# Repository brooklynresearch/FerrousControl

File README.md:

# FerrousControl
Ferrofluid controlled through an electromagnetic array

## python
This folder contains all the algorithms and code to send to the electromagnetic array.

## embedded
This folder contains all the design files and embedded code for the electromagentic controller boards.
These basically received USB Serial messages from the main computer, parse that information to the proper board, and translate those messages to the electromagnets.

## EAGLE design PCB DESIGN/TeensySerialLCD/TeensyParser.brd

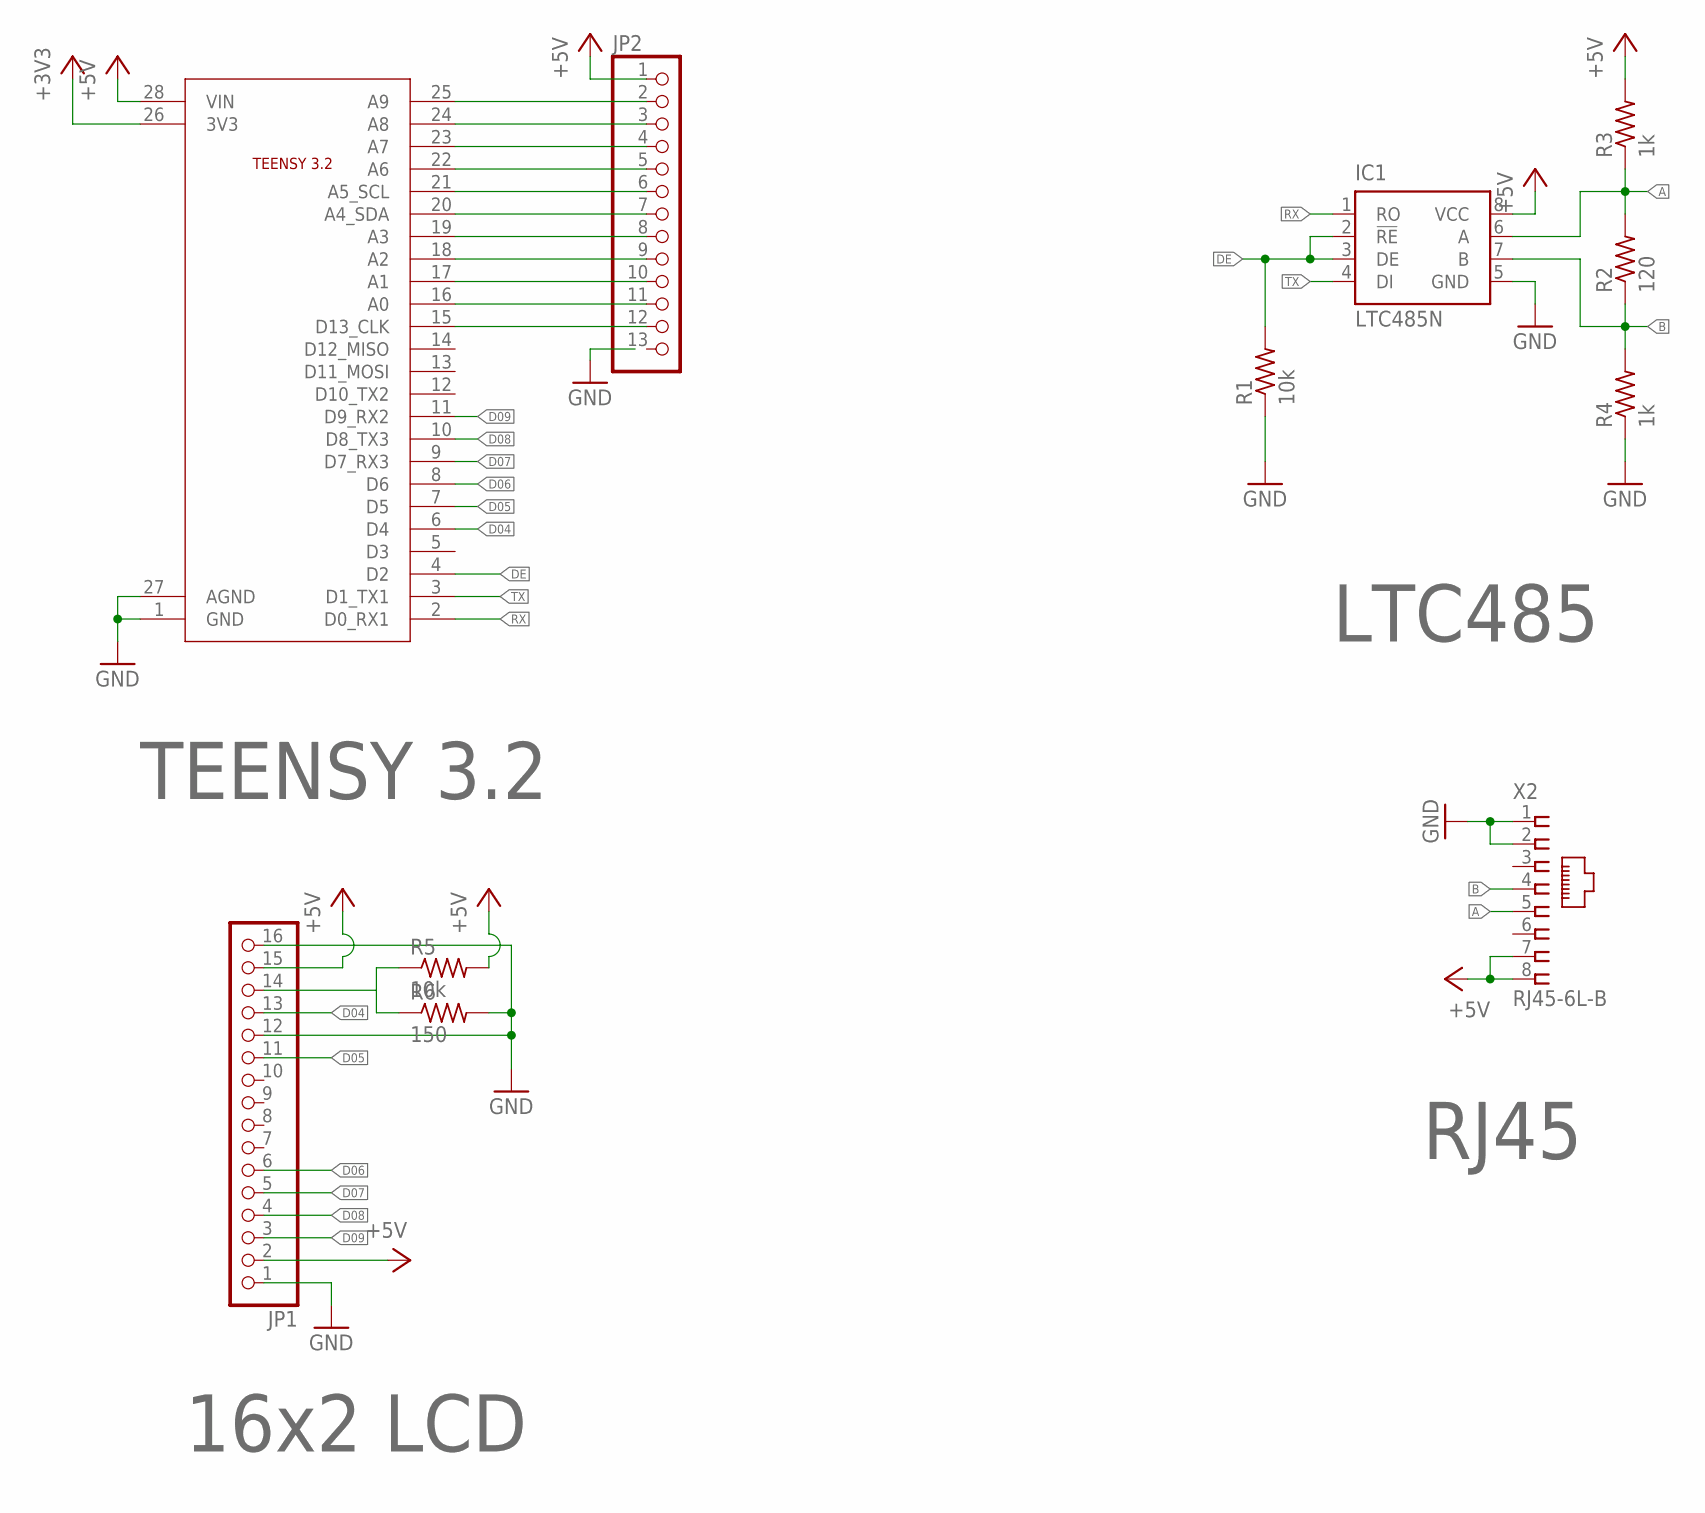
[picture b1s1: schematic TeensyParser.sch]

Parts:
IC1: LTC485N; DIL08
JP1: PINHD-1X16; 1X16
JP2: PINHD-1X13; 1X13
R1, R5: 10k; 0204/7
R2: 120; 0204/7
R3, R4: 1k; 0204/7
R6: 150; 0204/7
U$1: TEENSY3.2; TEENSY
X2: RJ45-6L-B; RJ45-NO-SHIELD

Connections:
+3V3: U$1.26 (3V3)
+5V: IC1.8 (VCC), JP1.2, JP1.15, JP2.1, R3.2, R5.2, U$1.28 (VIN), X2.7, X2.8
A: IC1.6 (A), R2.2, R3.1, X2.5
B: IC1.7 (B), R2.1, R4.2, X2.4
D04: JP1.13, U$1.6 (D4)
D05: JP1.11, U$1.7 (D5)
D06: JP1.6, U$1.8 (D6)
D07: JP1.5, U$1.9 (D7_RX3)
D08: JP1.4, U$1.10 (D8_TX3)
D09: JP1.3, U$1.11 (D9_RX2)
DE: IC1.2 (!RE), IC1.3 (DE), R1.2, U$1.4 (D2)
GND: IC1.5 (GND), JP1.1, JP1.12, JP1.16, R1.1, R4.1, R6.2, U$1.1 (GND), U$1.27 (AGND), X2.1, X2.2
unnamed: JP2.2, U$1.25 (A9)
unnamed: JP2.3, U$1.24 (A8)
unnamed: JP2.4, U$1.23 (A7)
unnamed: JP2.5, U$1.22 (A6)
unnamed: JP2.6, U$1.21 (A5_SCL)
unnamed: JP2.7, U$1.20 (A4_SDA)
unnamed: JP2.8, U$1.19 (A3)
unnamed: JP2.9, U$1.18 (A2)
unnamed: JP2.10, U$1.17 (A1)
unnamed: JP2.11, U$1.16 (A0)
unnamed: JP2.12, U$1.15 (D13_CLK)
unnamed: JP1.14, R5.1, R6.1
RX: IC1.1 (RO), U$1.2 (D0_RX1)
TX: IC1.4 (DI), U$1.3 (D1_TX1)

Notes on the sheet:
TEENSY 3.2
16x2 LCD
LTC485
RJ45

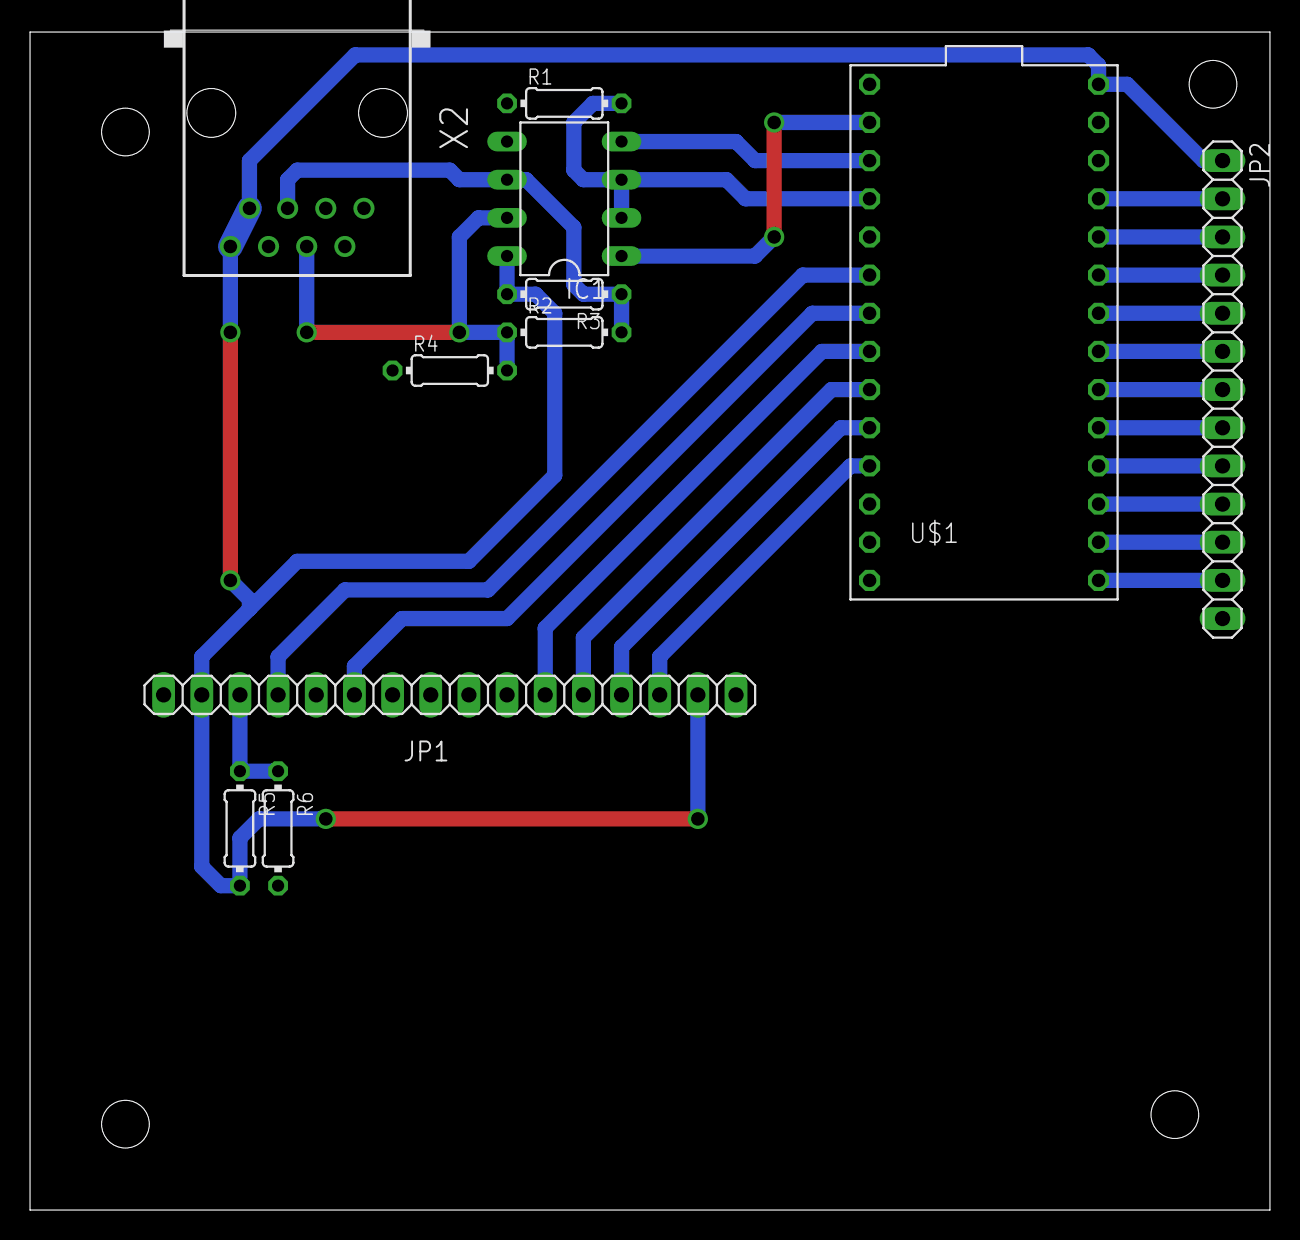
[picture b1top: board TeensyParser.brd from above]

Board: 2 copper layers, 82.5 x 78.4 mm, 11 parts (0 on the bottom side), 25 nets.

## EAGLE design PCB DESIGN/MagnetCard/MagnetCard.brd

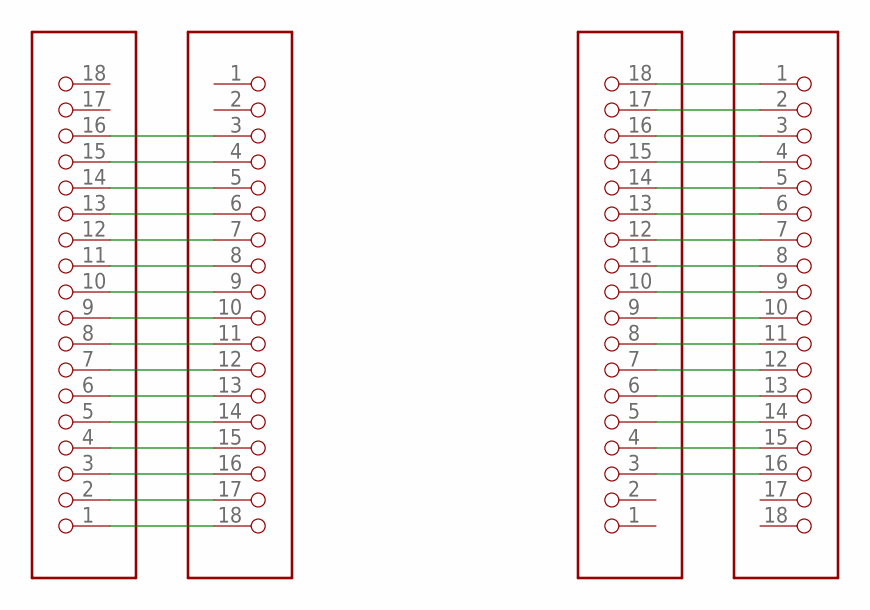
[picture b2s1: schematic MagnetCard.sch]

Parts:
U$1, U$2, U$3, U$4: 18X1_CARD_PADLONG; 18X1_CARDPAD_LONG

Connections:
unnamed: U$1.18, U$2.1
unnamed: U$1.17, U$2.2
unnamed: U$1.16, U$2.3
unnamed: U$1.15, U$2.4
unnamed: U$1.14, U$2.5
unnamed: U$1.13, U$2.6
unnamed: U$1.12, U$2.7
unnamed: U$1.11, U$2.8
unnamed: U$1.10, U$2.9
unnamed: U$1.9, U$2.10
unnamed: U$1.8, U$2.11
unnamed: U$1.7, U$2.12
unnamed: U$1.6, U$2.13
unnamed: U$1.5, U$2.14
unnamed: U$1.4, U$2.15
unnamed: U$1.3, U$2.16
unnamed: U$3.16, U$4.3
unnamed: U$3.15, U$4.4
unnamed: U$3.14, U$4.5
unnamed: U$3.13, U$4.6
unnamed: U$3.12, U$4.7
unnamed: U$3.11, U$4.8
unnamed: U$3.10, U$4.9
unnamed: U$3.9, U$4.10
unnamed: U$3.8, U$4.11
unnamed: U$3.7, U$4.12
unnamed: U$3.6, U$4.13
unnamed: U$3.5, U$4.14
unnamed: U$3.4, U$4.15
unnamed: U$3.3, U$4.16
unnamed: U$3.2, U$4.17
unnamed: U$3.1, U$4.18

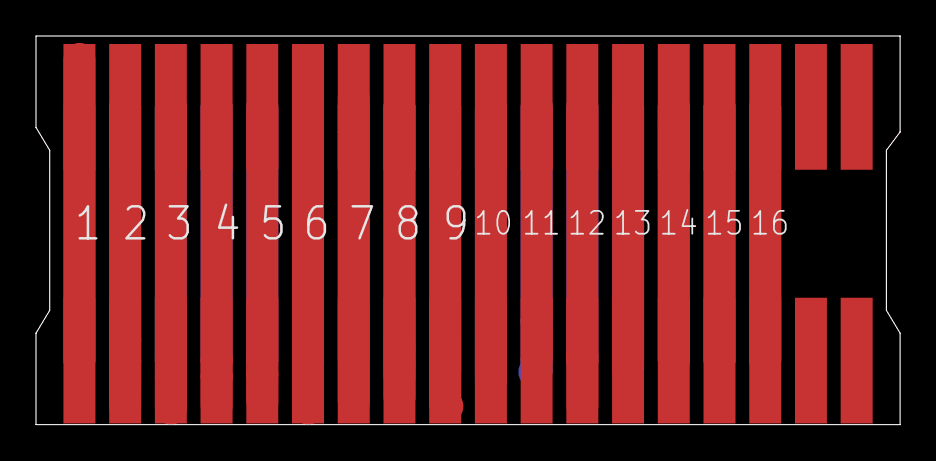
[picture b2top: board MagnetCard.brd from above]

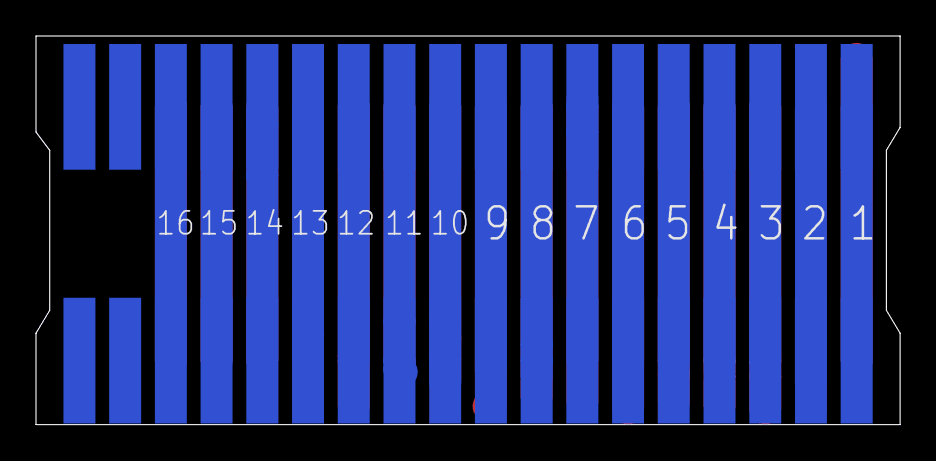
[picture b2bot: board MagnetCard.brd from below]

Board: 2 copper layers, 48.0 x 21.6 mm, 4 parts (2 on the bottom side), 32 nets.

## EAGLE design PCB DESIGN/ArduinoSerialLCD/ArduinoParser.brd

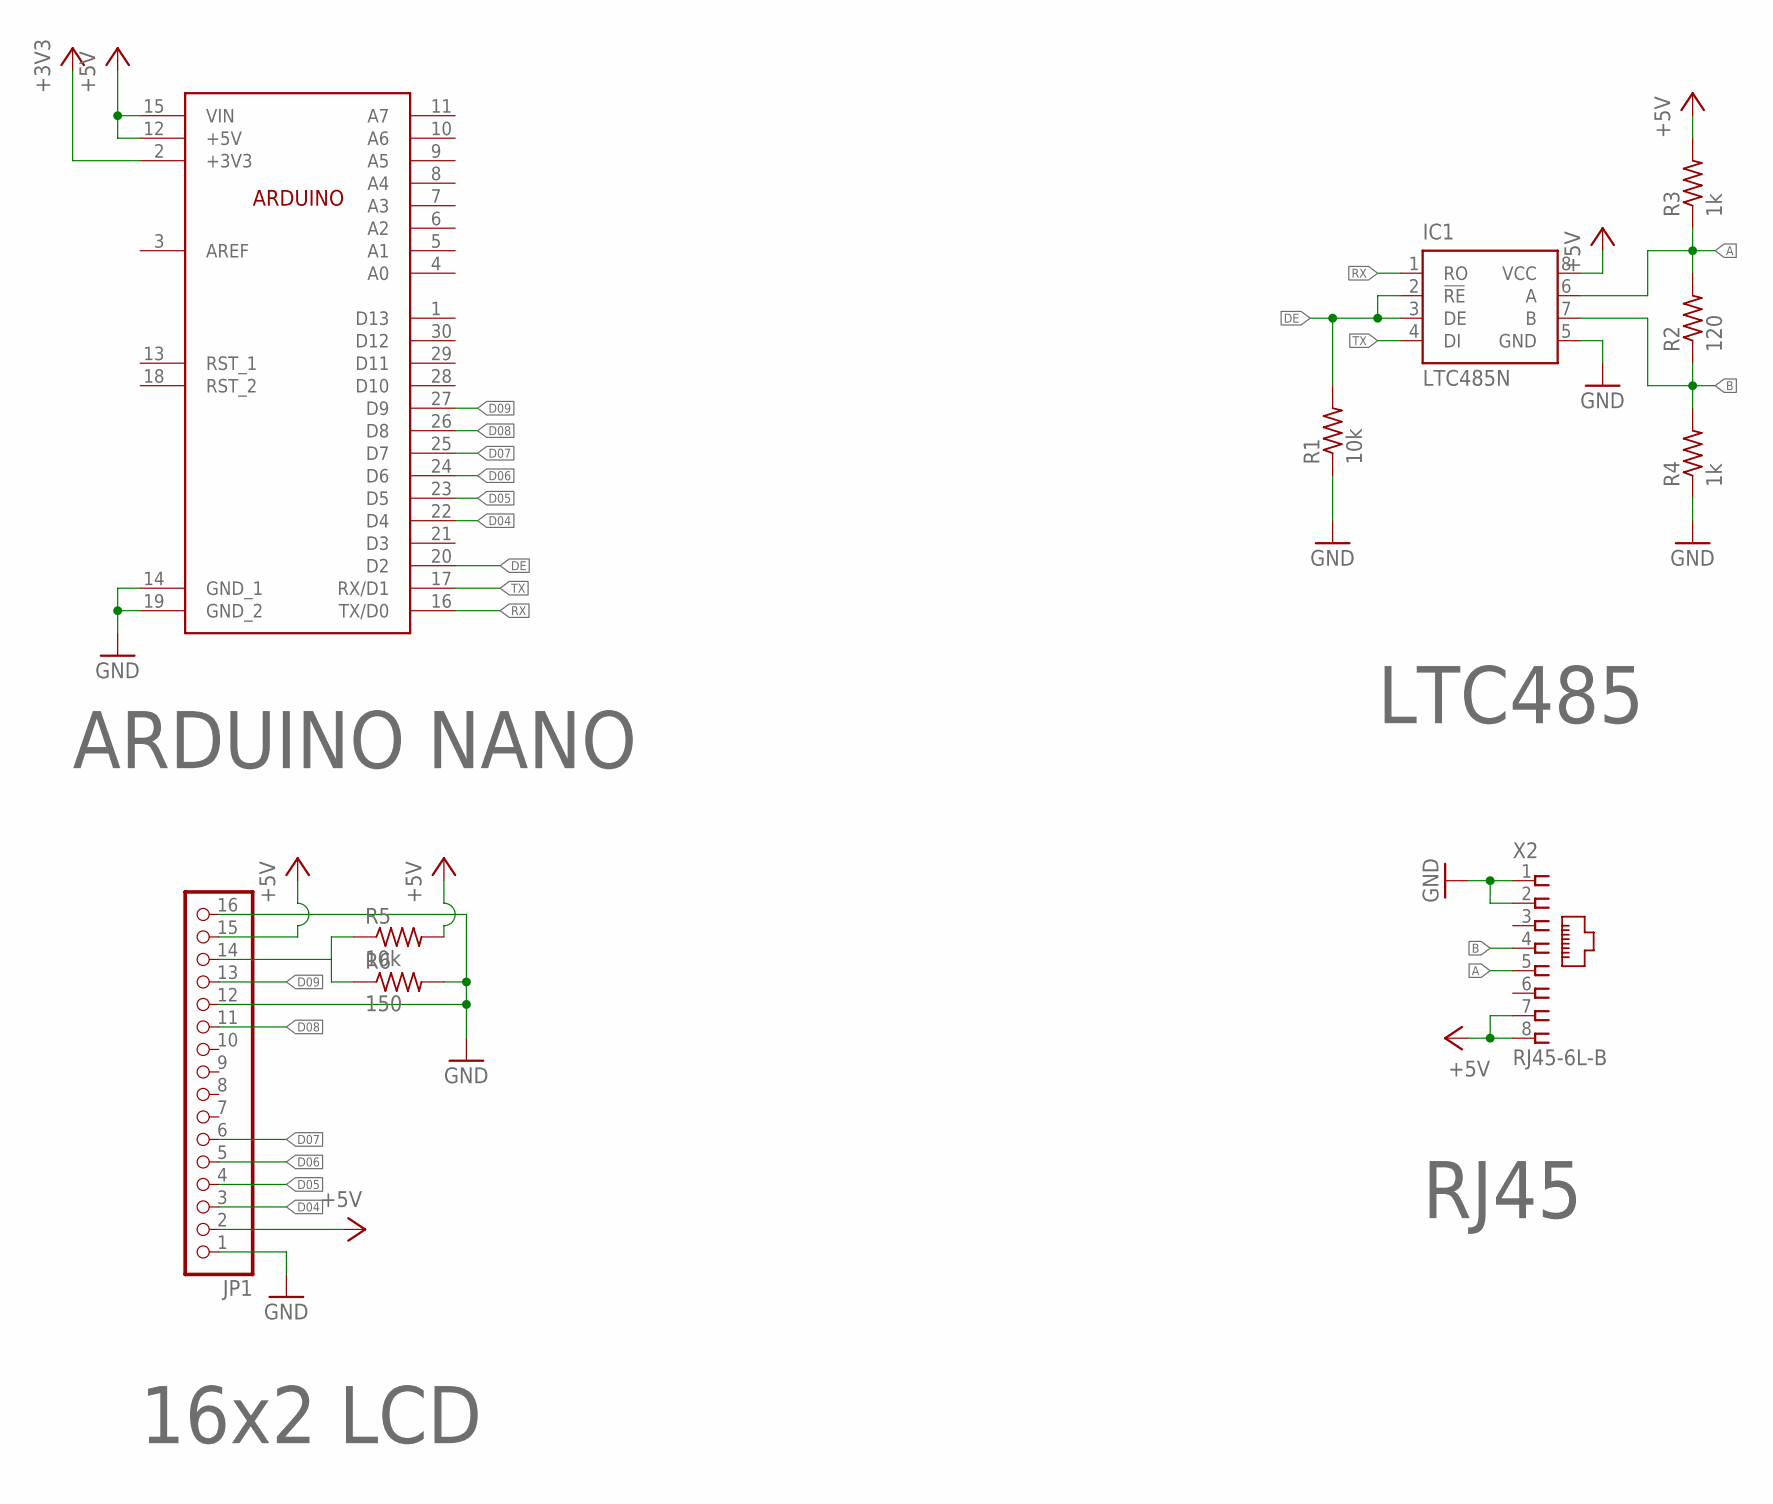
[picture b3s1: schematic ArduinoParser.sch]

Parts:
IC1: LTC485N; DIL08
JP1: PINHD-1X16; 1X16
R1, R5: 10k; 0204/7
R2: 120; 0204/7
R3, R4: 1k; 0204/7
R6: 150; 0204/7
U$2: ARDUINONANO; ARDUINO
X2: RJ45-6L-B; RJ45-NO-SHIELD

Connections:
+3V3: U$2.2 (+3V3)
+5V: IC1.8 (VCC), JP1.2, JP1.15, R3.2, R5.2, U$2.12 (+5V), U$2.15 (VIN), X2.7, X2.8
A: IC1.6 (A), R2.2, R3.1, X2.5
B: IC1.7 (B), R2.1, R4.2, X2.4
D04: JP1.3, U$2.22 (D4)
D05: JP1.4, U$2.23 (D5)
D06: JP1.5, U$2.24 (D6)
D07: JP1.6, U$2.25 (D7)
D08: JP1.11, U$2.26 (D8)
D09: JP1.13, U$2.27 (D9)
DE: IC1.2 (!RE), IC1.3 (DE), R1.2, U$2.20 (D2)
GND: IC1.5 (GND), JP1.1, JP1.12, JP1.16, R1.1, R4.1, R6.2, U$2.14 (GND_1), U$2.19 (GND_2), X2.1, X2.2
unnamed: JP1.14, R5.1, R6.1
RX: IC1.1 (RO), U$2.16 (TX/D0)
TX: IC1.4 (DI), U$2.17 (RX/D1)

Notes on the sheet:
ARDUINO NANO
16x2 LCD
LTC485
RJ45

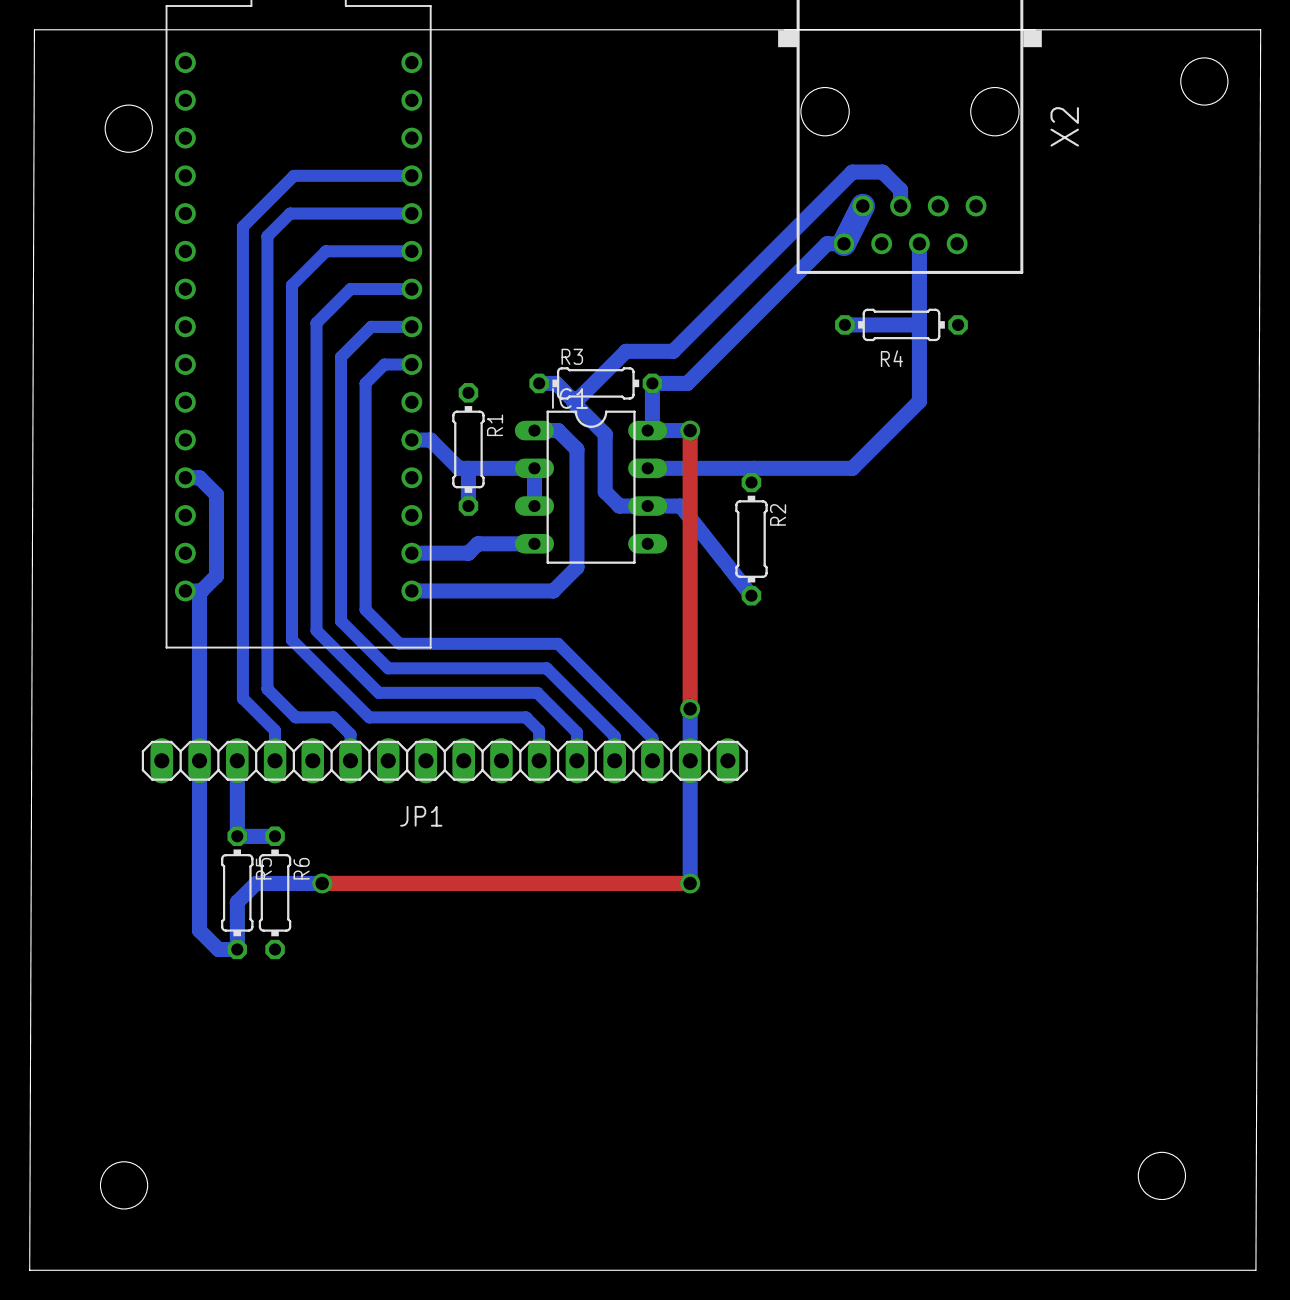
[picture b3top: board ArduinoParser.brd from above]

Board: 2 copper layers, 82.8 x 83.5 mm, 10 parts (0 on the bottom side), 14 nets.

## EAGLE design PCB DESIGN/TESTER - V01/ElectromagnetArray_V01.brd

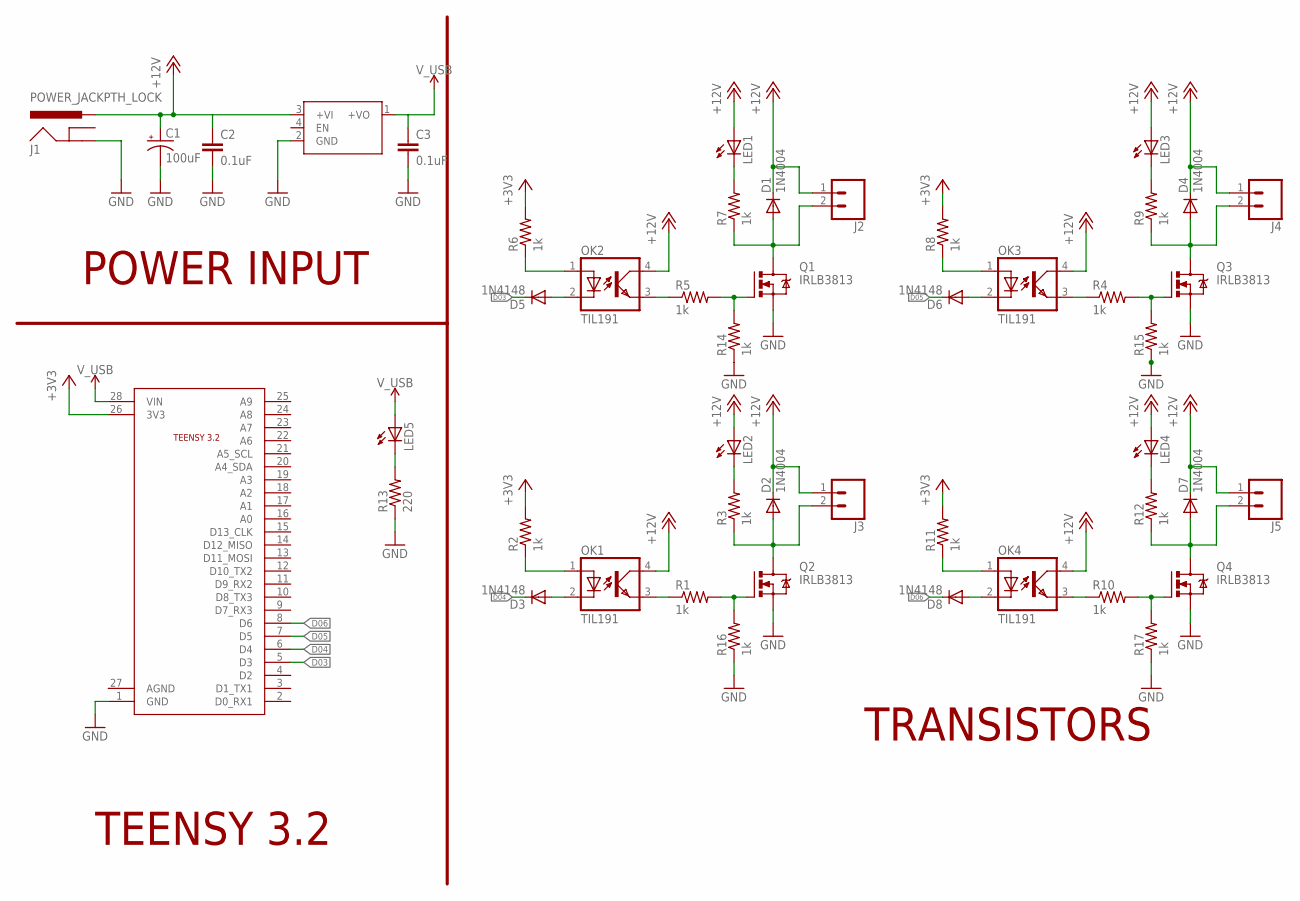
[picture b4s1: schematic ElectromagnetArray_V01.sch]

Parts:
C1: 100uF; E3,5-8
C2, C3: 0.1uF; C050-025X075
D1, D2, D4, D7: 1N4004; DO41-10
D3, D5, D6, D8: 1N4148; DO35-10
J1: POWER_JACKPTH_LOCK; POWER_JACK_PTH_LOCK
J2, J3, J4, J5: CONN_025MM; SCREWTERMINAL-5MM-2
LED1, LED2, LED3, LED4, LED5: LED5MM
OK1, OK2, OK3, OK4: TIL191; DIL04
Q1, Q2, Q3, Q4: IRLB3813; TO220BV
R1, R2, R3, R4, R5, R6, R7, R8, R9, R10, R11, R12, R14, R15, R16, R17: 1k; 0204/7
R13: 220; 0204/7
U$1: TEENSY3.2; TEENSY
U$2: SMPS_SMALL

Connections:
+3V3: R2.2, R6.2, R8.2, R11.2, U$1.26 (3V3)
+12V: C1.+, C2.1, D1.C, D2.C, D4.C, D7.C, J1.PWR, J2.1, J3.1, J4.1, J5.1, LED1.A, LED2.A, LED3.A, LED4.A, OK1.4 (COL), OK2.4 (COL), OK3.4 (COL), OK4.4 (COL), U$2.3 (+VI)
D03: D5.C, U$1.5 (D3)
D04: D3.C, U$1.6 (D4)
D05: D6.C, U$1.7 (D5)
D06: D8.C, U$1.8 (D6)
GND: C1.-, C2.2, C3.2, J1.GND, Q1.S, Q2.S, Q3.S, Q4.S, R13.1, R14.1, R15.1, R16.1, R17.1, U$1.1 (GND), U$2.2 (GND)
unnamed: Q1.G, R5.2, R14.2
unnamed: D2.A, J3.2, Q2.D, R3.1
unnamed: OK1.3 (EMIT), R1.1
unnamed: OK1.1 (A), R2.1
unnamed: D3.A, OK1.2 (C)
unnamed: LED2.K (C), R3.2
unnamed: Q2.G, R1.2, R16.2
unnamed: D4.A, J4.2, Q3.D, R9.1
unnamed: D1.A, J2.2, Q1.D, R7.1
unnamed: LED1.K (C), R7.2
unnamed: OK3.3 (EMIT), R4.1
unnamed: OK2.3 (EMIT), R5.1
unnamed: OK2.1 (A), R6.1
unnamed: D5.A, OK2.2 (C)
unnamed: OK3.1 (A), R8.1
unnamed: D6.A, OK3.2 (C)
unnamed: LED3.K (C), R9.2
unnamed: D7.A, J5.2, Q4.D, R12.1
unnamed: OK4.3 (EMIT), R10.1
unnamed: OK4.1 (A), R11.1
unnamed: D8.A, OK4.2 (C)
unnamed: LED4.K (C), R12.2
unnamed: Q4.G, R10.2, R17.2
unnamed: LED5.K (C), R13.2
unnamed: Q3.G, R4.2, R15.2
V_USB: C3.1, LED5.A, U$1.28 (VIN), U$2.1 (+VO)

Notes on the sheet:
TEENSY 3.2
TRANSISTORS
POWER INPUT

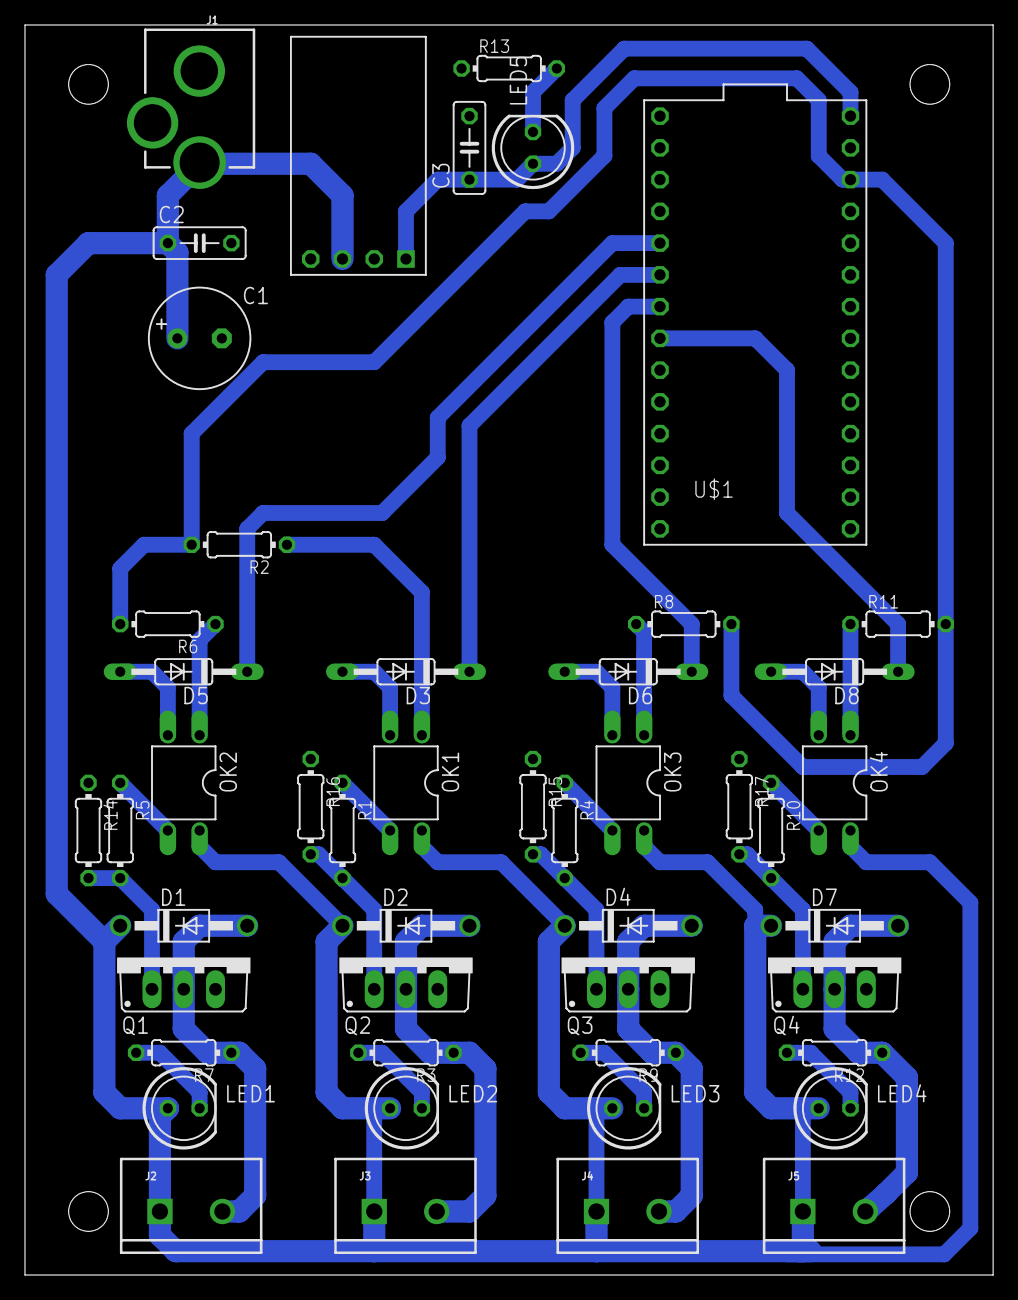
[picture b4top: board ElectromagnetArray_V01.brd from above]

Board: 2 copper layers, 77.5 x 100.0 mm, 48 parts (0 on the bottom side), 33 nets.

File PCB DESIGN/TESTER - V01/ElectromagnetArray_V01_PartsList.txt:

Partlist

Exported from ElectromagnetArray_V01.sch at 2/6/2019 3:11 PM

EAGLE Version 9.0.1 Copyright (c) 1988-2018 Autodesk, Inc.

Assembly variant: 

Part     Value              Device             Package             Library             Sheet

C1       100uF              CPOL-USE3.5-8      E3,5-8              rcl                 1
C2       0.1uF              C-EU050-025X075    C050-025X075        rcl                 1
C3       0.1uF              C-EU050-025X075    C050-025X075        rcl                 1
D1       1N4004             1N4004             DO41-10             diode               1
D2       1N4004             1N4004             DO41-10             diode               1
D3       1N4148             1N4148DO35-10      DO35-10             diode               1
D4       1N4004             1N4004             DO41-10             diode               1
D5       1N4148             1N4148DO35-10      DO35-10             diode               1
D6       1N4148             1N4148DO35-10      DO35-10             diode               1
D7       1N4004             1N4004             DO41-10             diode               1
D8       1N4148             1N4148DO35-10      DO35-10             diode               1
J1       POWER_JACKPTH_LOCK POWER_JACKPTH_LOCK POWER_JACK_PTH_LOCK SparkFun-Connectors 1
J2                          CONN_025MM         SCREWTERMINAL-5MM-2 SparkFun-Connectors 1
J3                          CONN_025MM         SCREWTERMINAL-5MM-2 SparkFun-Connectors 1
J4                          CONN_025MM         SCREWTERMINAL-5MM-2 SparkFun-Connectors 1
J5                          CONN_025MM         SCREWTERMINAL-5MM-2 SparkFun-Connectors 1
LED1                        LED5MM             LED5MM              led                 1
LED2                        LED5MM             LED5MM              led                 1
LED3                        LED5MM             LED5MM              led                 1
LED4                        LED5MM             LED5MM              led                 1
LED5                        LED5MM             LED5MM              led                 1
OK1      TIL191             TIL191             DIL04               optocoupler         1
OK2      TIL191             TIL191             DIL04               optocoupler         1
OK3      TIL191             TIL191             DIL04               optocoupler         1
OK4      TIL191             TIL191             DIL04               optocoupler         1
Q1       IRLB3813           IRF740             TO220BV             transistor-power    1
Q2       IRLB3813           IRF740             TO220BV             transistor-power    1
Q3       IRLB3813           IRF740             TO220BV             transistor-power    1
Q4       IRLB3813           IRF740             TO220BV             transistor-power    1
R1       1k                 R-US_0204/7        0204/7              rcl                 1
R2       1k                 R-US_0204/7        0204/7              rcl                 1
R3       1k                 R-US_0204/7        0204/7              rcl                 1
R4       1k                 R-US_0204/7        0204/7              rcl                 1
R5       1k                 R-US_0204/7        0204/7              rcl                 1
R6       1k                 R-US_0204/7        0204/7              rcl                 1
R7       1k                 R-US_0204/7        0204/7              rcl                 1
R8       1k                 R-US_0204/7        0204/7              rcl                 1
R9       1k                 R-US_0204/7        0204/7              rcl                 1
R10      1k                 R-US_0204/7        0204/7              rcl                 1
R11      1k                 R-US_0204/7        0204/7              rcl                 1
R12      1k                 R-US_0204/7        0204/7              rcl                 1
R13      220                R-US_0204/7        0204/7              rcl                 1
R14      1k                 R-US_0204/7        0204/7              rcl                 1
R15      1k                 R-US_0204/7        0204/7              rcl                 1
R16      1k                 R-US_0204/7        0204/7              rcl                 1
R17      1k                 R-US_0204/7        0204/7              rcl                 1
U$1      TEENSY3.2          TEENSY3.2          TEENSY              EzerLonginus        1
U$2      SMPS_SMALL         SMPS_SMALL         SMPS_SMALL          EzerLonginus        1

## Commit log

2019-02-05 Tester Board
    Eagle files for the intial tester board for a small electromagnetic array.
2019-02-05 Initial Tester Pictures
    Board, mount, and electromagnet pictures
2019-02-06 Updates to Preliminary Design
    Added pull down resistors for the Gate Input on the Transistors.
    All opto isolator LEDs are on the 3V3 rail
2019-02-07 Othermill Fix
    Updated layout design for othermill
2019-03-04 Serial Communication
    Basic Serial Communication between the system and magnetic array
2019-03-04 Fixed Readme
    Readme Fix
2019-07-20 Serial Communications Test
    Added Teensy Code, Arduino Code, and the current state of the python code.
2019-07-20 Serial PCBs
    Arduino Nano Serial PCB, Teensy Serial PCB, with images of schematic and layout.
2019-07-22 Serial Line Update
    Serial1.write Change
2019-07-26 320 bytes; checksum for debug
2019-07-31 Updated Teensy Code
2019-08-04 ersatz nstokes copier
    This is not necessarily helpful
2019-08-05 Teensy 3.6 Code
    Code for the Teensy 3.6
2019-08-05 temprunner
    great
2019-08-05 modified nstokes_participle for 1600 value send
    - removed previous WIP version of nstokes
    - added new nstokes_particle folder sent from Jacob
    - modified to compile data and then hand off to thread to send on serial
    - thread only receives new data from draw loop if thread is not busy
    - modified ratio function to fit within 0 to 127
    - found snake / snek function sends negative values so ratio function now zeros those out
2019-08-05 altered teensy code from one large buffer to five smaller ones split among serial
    As in title, maybe a good idea to make it pretty
2019-08-06 new amoeba logic, list reordering, serial bus baud rate changes and writes
    - amoeba directional values changes now, but will still fail eventually
    - ordering of list / bytestring sent to teensy changed to reflect message ordinance
    - serial baud rate and pin changes
2019-08-12 Added Final Arduino Code for each of the Panels
    Final Arduino Code for each of the panels.
2019-08-12 Added some comments
2019-08-12 Runs around 7 frames per second, but seems like the full test
    This version runs at around 7 frames per second, but seems to send the full complement accuratelyg
    Notes that baud rate has been increased to 2000000
2019-08-12 Switch back to 1000000 baud rate for teensy / mac
    switched back to 1000000 on Teensy-Mac comms for now in case there is legacy code out there using 10000000
2019-08-12 127 check
    safety check
2019-08-12 Infeed from test branch
    Stalls without delay from five teensies, possibly stalls here as well
2019-08-12 Ignoring .DS_Store
    Annoying
2019-08-12 fixed float issue with ratio
    ratio in non upper and lower bounds was creating floats sometimes
2019-08-13 Testing Mode Added
2019-08-13 Put safety bounds [0,127] into the testing branch
    Put this in testing branch; we need a system for keeping branches straight for stuff like this
2022-03-02 Initial Update V2
    Initial Updated Code, Schematics, and ReadMe for Version 02
2022-03-04 Updated Controller Board Defines
    Changed the Baud Rate, Commented out the BOARD_TEST, and updated the LCD to reflect the changes
2022-03-05 remove delay, fix serial port mapping
2022-03-05 test sequence working
2022-03-05 Start with test sequence
2022-03-08 fix tile mappings, other stuff
2022-03-08 add settings() function and libraries folder to make it cli-launchable
2022-03-08 swap parser positions to match board labels
2022-03-08 add readme
2022-04-05 Updates
    Changed steps (speed of snake), decay rate, framerate from 25 to 30, added var names for mode time intervals
2022-04-13 Small tweaks
2022-04-18 Zero Out Magnets without Serial
    Zero out the magnets incase we lose connection with computer or USB signal.
2022-04-24 Blooming in place
    - Some errata cleaned up
    - Some formatting changes for readability
    - Added in blooming behavior
    - Added blooming timer to trigger every three works
2022-04-25 Fullbloom update
    - short full bloom
    - extra logic for sudden off
2023-07-12 pcb, production, and software files for the embedded system
2023-07-14 reformatted python folders
2023-08-03 Added Serial Parser BOM

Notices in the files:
parts and their libraries:
SparkFun-Connectors: Licensing: Creative Commons ShareAlike 4.0 International - https://creativecommons.org/licenses/by-sa/4.0
